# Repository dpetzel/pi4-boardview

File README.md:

# Raspberry Pi 4 Model B board reconstruction

A KiCad 10 reconstruction of the Raspberry Pi 4 Model B board (part placement, part identification, nets traced from
real boards), published as interactive boardviews for repair work. Each board revision is reconstructed separately.

> [!WARNING]
> **Unofficial, incomplete and possibly wrong.**
> * **Not official.** Not made, endorsed or checked by Raspberry Pi Ltd, and not based on official schematics or layout
>   files. "Raspberry Pi" is a trademark of Raspberry Pi Ltd; this project is not affiliated with it.
> * **Made by a hobbyist.** Reverse engineered by an untrained hobbyist from photos and multimeter probing, not by an
>   electronics professional.
> * **Incomplete and possibly wrong.** Many parts are unidentified and most nets are untraced. Positions, values, part
>   numbers and connections may be wrong, and your board may differ.
> * **Use at your own risk.** Board-level repair can destroy hardware and can be dangerous. Check everything against
>   your own board, your own measurements and the manufacturers' datasheets before you solder or apply power. Provided
>   "as is" with no warranty of any kind; the authors and contributors accept no liability for any damage or injury.

* **View it:** <https://dpetzel.github.io/pi4-boardview/> lists the revisions, rebuilt from `main` on every push

| Revision | Viewer | Downloads (always the latest build) | Status |
|---|---|---|---|
| 1.4 | [pi4-boardview/1.4/](https://dpetzel.github.io/pi4-boardview/1.4/) | [HTML](https://dpetzel.github.io/pi4-boardview/1.4/pi4_rev_1.4-boardview.html) · [.brd](https://dpetzel.github.io/pi4-boardview/1.4/pi4_rev_1.4.brd) | In progress |
| 1.5 | [pi4-boardview/1.5/](https://dpetzel.github.io/pi4-boardview/1.5/) | [HTML](https://dpetzel.github.io/pi4-boardview/1.5/pi4_rev_1.5-boardview.html) · [.brd](https://dpetzel.github.io/pi4-boardview/1.5/pi4_rev_1.5.brd) | Started: DA9090 PMIC, C13, test points |

The HTML viewer is self-contained and works offline; the `.brd` is for
[OpenBoardView](https://github.com/OpenBoardView/OpenBoardView). To find a board's revision, run `grep Revision /proc/cpuinfo` on it:
the last digit of the code is the revision (`c03114` = rev 1.4, `c03115` = rev 1.5).

## Repository

| Path | What |
|---|---|
| `1.4/`, `1.5/` | One KiCad project per board revision (`pi4_rev_<rev>.kicad_pcb`, `.kicad_pro`, `.kicad_sch`). Top and bottom photos are embedded in each board as reference images (Eco1.User = top, Eco2.User = bottom) |
| `1.4/*.kicad_sch`, `1.4/pi4_rev_1.4.kicad_sym` | Rev 1.4 schematic (root sheet plus `board_only` and `top_ics` sub-sheets) and its symbols |
| `1.5/pi4_rev_1.5.kicad_sch` | Rev 1.5 schematic (so far the DA9090 PMIC and C13) |
| `lib/pi4_common.pretty/`, `lib/pi4_common.kicad_sym` | Footprints and symbols shared by all revisions (`${KIPRJMOD}/../lib` in each revision's lib tables), including both PMICs: MxL7704 (rev 1.4 and earlier) and DA9090 (rev 1.5) |
| `tools/boardview.py`, `tools/template.html` | Exporter for one board (HTML viewer + `.brd`) and the viewer it fills in |
| `tools/build_site.py`, `tools/index.html` | Builds every revision plus the landing page that lists them |
| `.github/workflows/boardview.yml` | CI: builds the boardviews and deploys them to Pages |

The boardview files are build output and not committed.

### Adding a revision

Make a folder named after the revision (e.g. `1.2/`) holding one KiCad project, `pi4_rev_1.2.kicad_pcb` with the
board photos embedded as reference images. Scale and place the photos so the mounting holes land where rev 1.4's do (top-left
hole at (103.5, 78.5) mm, 58 x 49 mm pattern): all revisions then share one coordinate frame and parts can be copied
between them. `build_site.py` picks up every top-level folder named like a version number,
so the new revision appears on the site and in every viewer's revision switcher on the next push. Add it to the table
above.

## Contributing

Edit a board in KiCad 10 and open a pull request. Part details go in footprint fields: `Function`, `Part`, `Notes`,
`Replacement`, and `Source` (`Source2`, `Source3`, … for more links). Fields holding a URL show as links in the
viewer. References ending in `**` or `?` (`REF**`, `R?`) are shown as unidentified parts.

Every pull request builds the boardviews. Download the `boardview` artifact from the PR's workflow run to check
your change before it's merged.

### Building locally

The exporter needs KiCad's `pcbnew` Python module. With Docker:

```sh
docker run --rm -v "$PWD":/w -w /w kicad/kicad:10.0 python3 tools/build_site.py
```

or with the Python bundled with KiCad (on Windows, `"C:\Program Files\KiCad\10.0\bin\python.exe"`):

```sh
python3 tools/build_site.py                       # all revisions -> _site/ (open _site/index.html)
python3 tools/boardview.py 1.4/pi4_rev_1.4.kicad_pcb   # one board -> 1.4/boardview/
```

Options for both: `-o DIR`, `--no-photo`, `--kicad-nets-only` (skip nets derived from copper; see the notes at the top
of `tools/boardview.py`). The revision switcher only shows when the site is served over http(s), e.g.
`python3 -m http.server -d _site`. KiCad exports the last *saved* board, so save before building.

## License

[CC-BY-SA-4.0](LICENSE): share and adapt with attribution, and publish adaptations under the same license.
The license's disclaimer of warranties and limitation of liability apply in full.

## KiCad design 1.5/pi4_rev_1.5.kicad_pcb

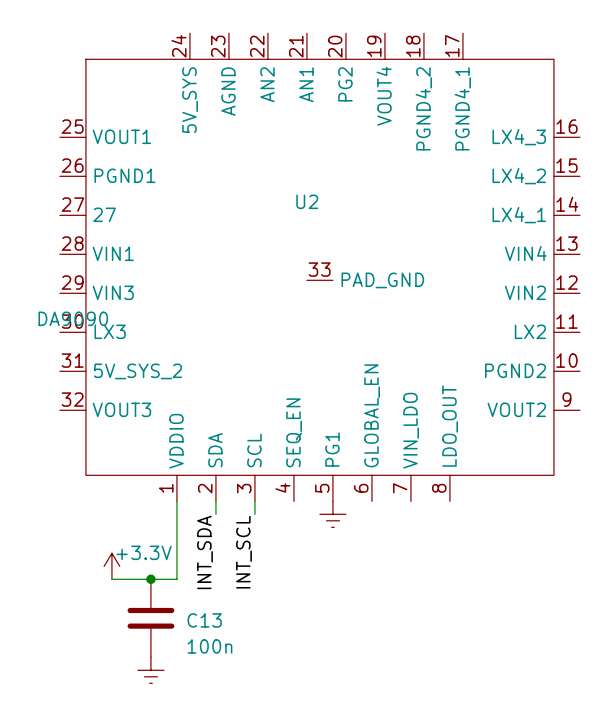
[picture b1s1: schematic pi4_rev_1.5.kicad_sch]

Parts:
C13: 100n; C_01005_0402Metric
U2: DA9090; FCQFN-32_5x5mm_P0.5mm_DA9090

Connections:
+3.3V: C13.1, U2.1 (VDDIO)
/INT_SCL: U2.3 (SCL)
/INT_SDA: U2.2 (SDA)
<NO NET>: C13.2, U2.5 (PG1)
unnamed: U2.14 (LX4_1), U2.15 (LX4_2), U2.16 (LX4_3)
unnamed: U2.17 (PGND4_1), U2.18 (PGND4_2)
unnamed: U2.28 (VIN1), U2.29 (VIN3)

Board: 2 copper layers, 24 parts (22 on the bottom side), 5 nets, no tracks yet.

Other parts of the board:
TP1, TP2, TP3, TP4, TP5, TP6, TP7, TP8, TP9, TP10, TP11, TP12, TP13, TP14, TP15, TP17, TP22, TP23, TP24, TP26, TP27, TP34: TestPoint_Pad_D2.0mm

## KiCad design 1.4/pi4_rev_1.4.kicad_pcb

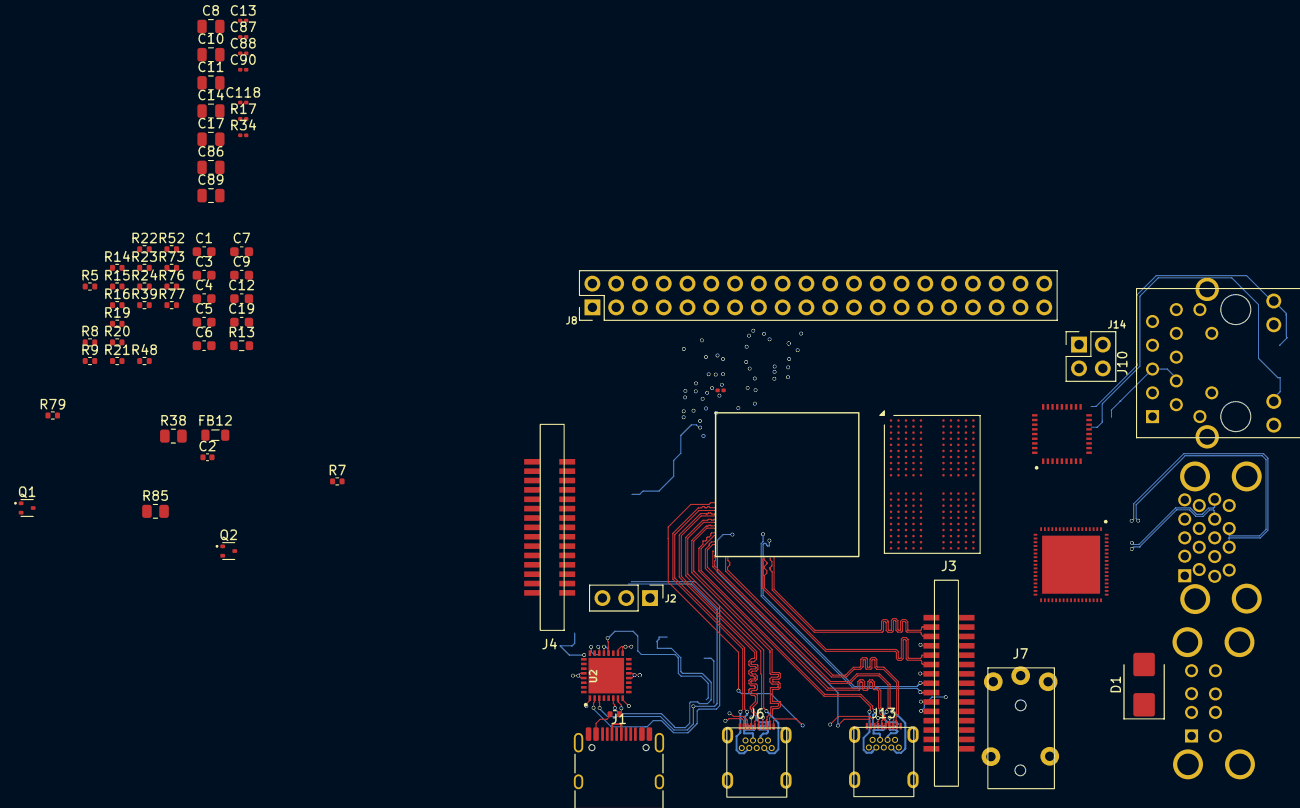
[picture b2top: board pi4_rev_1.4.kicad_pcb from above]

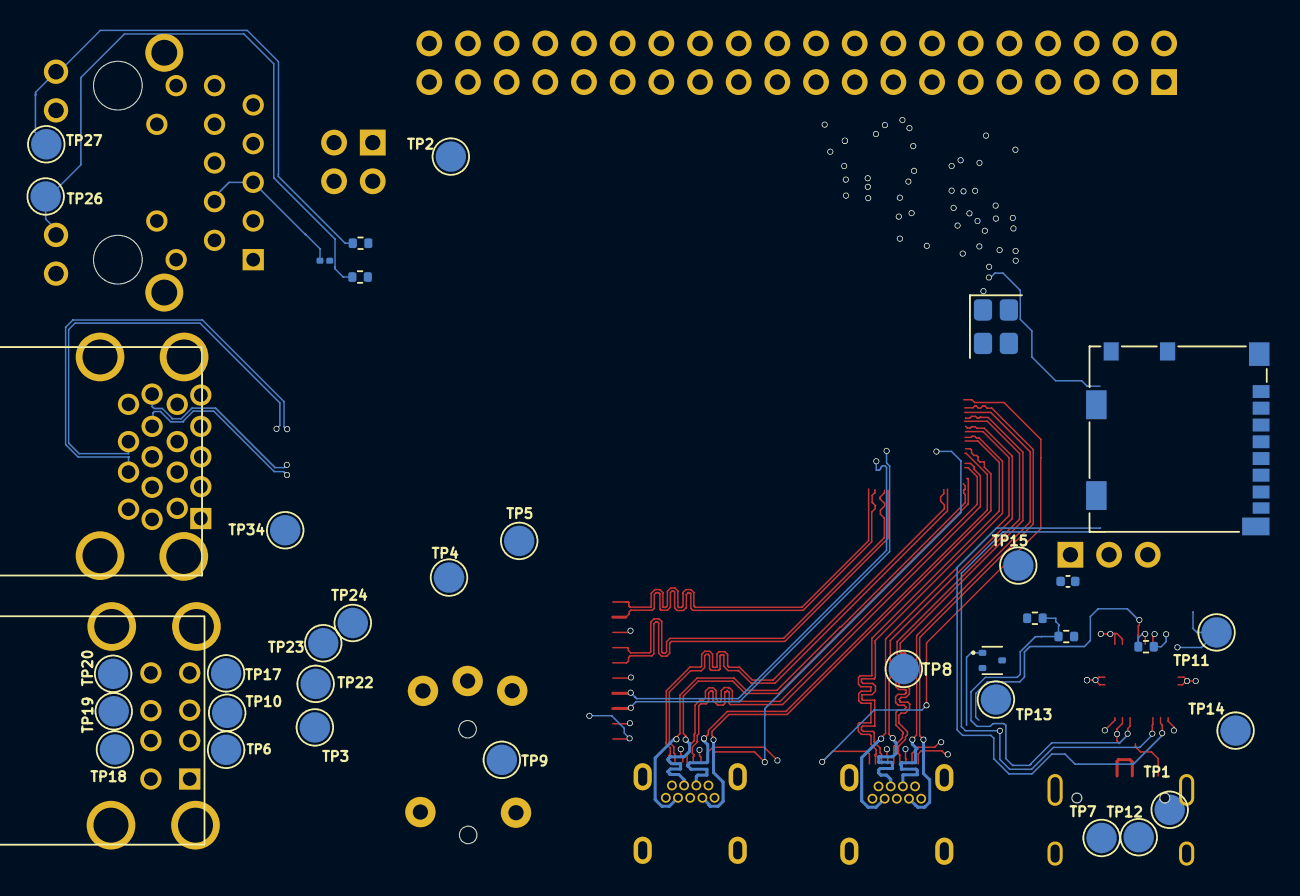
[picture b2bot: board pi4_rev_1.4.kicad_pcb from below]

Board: 2 copper layers, 105 parts (37 on the bottom side), 42 nets.

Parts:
C1, C12: 10u; C_0603_1608Metric
C2: 4u7; C_0402_1005Metric
C3, C4, C5, C6, C7, C9, C19: 22u; C_0603_1608Metric
C8, C10, C11, C14, C17, C86, C89: 47u; C_0805_2012Metric
C13, C87, C88, C90, C101, C118: 100n; C_0201_0603Metric
C18: 2u2; C_0402_1005Metric
D1: SMBJ5.0A-TR; D_SMB
FB12: 60R@100MHz; L_0805_2012Metric
J1: USB-C POWER IN; USB_C_Receptacle_HRO_TYPE-C-31-M-12
J2: RUN, GLOBAL_EN HEADER; PinHeader_1x03_P2.54mm_Vertical
J3: CAMERA; FFC_2x15_P1.0mm_Dual_Row_Pi4
J4: DISPLAY; FFC_2x15_P1.0mm_Dual_Row_Pi4
J6: MICRO HDMI 0; HDMI_Micro-D_Hybrid_10SMD_9TH_Pi4
J7: A/V JACK; Jack_AV_MTCONN_5TH_Pi4
J8: GPIO EXPANSION; PinHeader_2x20_P2.54mm_Vertical
J10: GIGABIT ETHERNET; RJ45_MagJack_LPJG0926_Layout
J11: Conn_USB_A_Stack_8P; USB_A_Stack_8P_Pi4_USB2
J12: Conn_USB_A_Stack_18P; USB_A_Stack_18P_Pi4_USB3
J13: MICRO HDMI 1; HDMI_Micro-D_Hybrid_10SMD_9TH_Pi4
J14: PoE HEADER; PinHeader_2x02_P2.54mm_Vertical
J9001: Molex_104031-0811; microSD_HC_Molex_104031-0811
Q1, Q2, Q5: DMG1012T; SOT-523
R1, R79: 5K1; R_0402_1005Metric
R2, R5: 10R; R_0402_1005Metric
R6: 100K; R_0402_1005Metric
R7, R9, R15: 10K; R_0402_1005Metric
R8: 9K1; R_0402_1005Metric
R10, R14, R20, R23, R76, R77: 100R; R_0402_1005Metric
R13: 470R; R_0603_1608Metric
R16: 140R; R_0402_1005Metric
R17, R34: 1K; R_0201_0603Metric
R19, R22, R39: 220R; R_0402_1005Metric
R21, R24, R52: 1K8; R_0402_1005Metric
R38, R85: 0R; R_0805_2012Metric
R43, R44: 470R; R_0402_1005Metric
R48, R73: NF; R_0402_1005Metric
R9001: 10; R_0201_0603Metric
TP1, TP2, TP3, TP4, TP7, TP8, TP9, TP11, TP12, TP13, TP14, TP15, TP22, TP23, TP24, TP26, TP27, TP34: R2MM; TestPoint_Pad_D2.0mm
TP5, TP6, TP10, TP17, TP18, TP19, TP20: TestPoint; TestPoint_Pad_D2.0mm
U2: MxL7704; QFN-32-1EP_5x5mm_P0.5mm_EP3.8x3.8mm_MxL7704
U9001: BCM2711; BCM2711_Outline_15x15mm
U9002: MT53E2G32D4NQ-046 WT:A; BGA-200_10x14.5mm_Layout12x22_P0.8x0.65mm
U9003: BCM54213PE; QFN-36_6x6mm_P0.5mm_NoEP_BCM54213PE
U9004: VL805-Q6; QFN-68-1EP_8x8mm_P0.4mm_EP6.2x6.2mm_VL805
Y9001: 54MHz; Crystal_SMD_3225-4Pin_3.2x2.5mm

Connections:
1V1_DDR: C8.1, R39.1, TP14.1 (1_1), U2.32 (VOUT3)
1V03_EN: R8.2, R15.1, U2.5 (PG1)
1V8: C6.1, R73.1, TP13.1 (1_1), U2.9 (VOUT2)
3V3: C4.1, C13.1, J3.15, J4.14, J4.15, J8.1, J8.17, J10.15, J10.17, R8.1, R9.1, R34.1, R38.2, R52.1, TP11.1 (1_1), U2.1 (VDDIO), U2.25 (VOUT1)
3V3_AUD: C2.1, C88.1, R48.1, TP4.1 (1_1), U2.8 (LDO_OUT)
5V: C3.1, C5.1, C7.1, C9.1, C19.1, D1.1 (K), J1.A4 (VBUS), J1.A9 (VBUS), J1.B4 (VBUS), J1.B9 (VBUS), J8.2, J8.4, R2.1, R5.1, R6.1, R7.1, TP1.1 (1_1), TP2.1 (1_1), TP3.1 (1_1), U2.12 (VIN2), U2.13 (VIN4), U2.28 (VIN1), U2.29 (VIN3)
5V_HDMI: J6.19 (+5V), J13.19 (+5V)
/1V03: C17.1, FB12.1, R14.1, R76.1, R85.1, TP34.1 (1_1)
/5V_SYS: C12.1, R5.2, U2.24 (5V_SYS), U2.31 (5V_SYS_2)
/AUDIO_L: C86.2, J7.4, R21.1, TP22.1 (1_1)
/AUDIO_R: C89.2, J7.3, R24.1, TP23.1 (1_1)
/Board only/NET_TP6: J11.3, TP6.1 (1_1)
/Board only/NET_TP10: J11.2, TP10.1 (1_1)
/Board only/NET_TP18: J11.7, TP18.1 (1_1)
/Board only/NET_TP19: J11.6, TP19.1 (1_1)
/LX4: U2.14 (LX4_1), U2.15 (LX4_2), U2.16 (LX4_3)
/USB_CC: J1.A5 (CC1), J1.B5 (CC2), R1.1, R79.1
/VIN_LDO: C1.1, R2.2, U2.7 (VIN_LDO)
GLOBAL_EN: C18.1, J2.1, R6.2, R10.1, U2.6 (GLOBAL_EN)
GND: C1.2, C2.2, C3.2, C4.2, C5.2, C6.2, C7.2, C8.2, C9.2, C10.2, C11.2, C12.2, C13.2, C14.2, C17.2, C18.2, C19.2, C87.2, C88.2, C90.2, C101.2, C118.2, D1.2 (A), J1.A1 (GND), J1.A12 (GND), J1.B1 (GND), J1.B12 (GND), J1.SH (SHELL3), J2.2, J3.1, J3.4, J3.7, J3.10, J4.1, J4.4, J4.7, J4.10, J4.13, J6.4 (D2_SH), J6.7 (D1_SH), J6.10 (D0_SH), J6.13 (CLK_SH), J6.16 (GND), J6.20 (SH1), J6.21 (SH2), J6.22 (SH3), J6.23 (SH4), J8.6, J8.9, J8.14, J8.20, J8.25, J8.30, J8.34, J8.39, J10.19 (SHELL), J10.20 (SHELL), J13.4 (D2_SH), J13.7 (D1_SH), J13.10 (D0_SH), J13.13 (CLK_SH), J13.16 (GND), J13.20 (SH1), J13.21 (SH2), J13.22 (SH3), J13.23 (SH4), Q1.2 (S), Q2.2 (S), Q5.2 (S), R13.2, R15.2, R16.2, R20.2, R21.2, R23.2, R24.2, R39.2, R48.2, R52.2, R73.2, R76.2, R79.2, TP7.1 (1_1), TP8.1 (1_1), TP9.1 (1_1), TP12.1 (1_1), TP17.1 (1_1), TP20.1 (1_1), U2.10 (PGND2), U2.17 (PGND4_1), U2.18 (PGND4_2), U2.22 (AN2), U2.23 (AGND), U2.26 (PGND1), U2.33 (PAD_GND), Y9001.2 (G), Y9001.4 (G)
unnamed: C86.1, C87.1, R19.2, R20.1
unnamed: C89.1, C90.1, R22.2, R23.1
unnamed: C101.1, J10.4, J10.5
unnamed: Q1.3 (D), R17.2
unnamed: J10.16, R43.1, TP26.1 (1_1)
unnamed: J10.18, R44.1, TP27.1 (1_1)
unnamed: Q5.3 (D), R10.2
unnamed: R7.2, U2.4 (SEQ_EN)
unnamed: R14.2, R16.1
PD_SENSE: R1.2, U2.21 (AN1)
RUN: C118.1, R9.2, R77.2
RUN_PG2: J2.3, R77.1, U2.20 (PG2)
SCL0: J3.13, J4.11
SDA0: J3.14, J4.12
TR0_TAP: J10.11 (VC1), J14.2
TR1_TAP: J10.12 (VC2), J14.1
TR2_TAP: J10.13 (VC3), J14.4
TR3_TAP: J10.14 (VC4), J14.3
UUSB_D_N: J1.A7 (D1_N), J1.B7 (D2_N)
UUSB_D_P: J1.A6 (D1_P), J1.B6 (D2_P)
VDD_CORE: C10.1, C11.1, C14.1, TP15.1 (1_1), U2.19 (VOUT4)
WB_VBAT: R13.1, R17.1
